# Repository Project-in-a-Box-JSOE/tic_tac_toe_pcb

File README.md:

# Tic-Tac-Toe

**A project series hosted by Project in a Box at UCSD**
> Workshop documentation [Tic-Tac-Toe Guide](https://docs.google.com/presentation/d/1Ihq2s2tMd88KeOKXIFUcY-OSz5jwRyJ442QZBEG7MqE/edit#slide=id.g12576c3175b_0_320)<br />
> More about [Project in a Box](https://pibucsd.org/)

## Overview
This workshop is oriented to assembling a handheld Tic-Tac-Toe board with surface mount devices (SMD) and reflow soldering.

The PCB was designed in Autodesk EAGLE

## BOM

| Component                    | Vendor                                                                                                     | Quantity   |
| ---------------------------- | ---------------------------------------------------------------------------------------------------------- | ---------- |
| NeoPixel Reverse Mount LEDs  | [Digikey](https://www.digikey.com/en/products/detail/adafruit-industries-llc/4960/14302512)                | 9          |
| ATMEGA328P-AUR              | [Digikey](https://www.digikey.com/en/products/detail/microchip-technology/ATMEGA328P-AUR/2357086)         | 1          |
| Tactile SMD Switch           | [Digikey](https://www.digikey.com/en/products/detail/te-connectivity-alcoswitch-switches/FSMSMTR/529671)   | 10         | 
| 5V-Regulator NCP1117ST50T3G  | [Digikey](https://www.digikey.com/en/products/detail/onsemi/NCP1117ST50T3G/1967217?utm_adgroup=Integrated%20Circuits%20%28ics%29&utm_source=google&utm_medium=cpc&utm_campaign=Shopping_Supplier_onsemi&utm_term=&utm_content=Integrated%20Circuits%20%28ics%29&gclid=Cj0KCQiAlMCOBhCZARIsANLid6Y771XCwKb85bAQFjVsh4KLFg09zcmp8NNUzVosYromvapvGWj7TFYaAqMzEALw_wcB)                                         | 1          | 
| Male Header (2x3-pins)       | [Digikey](https://www.digikey.com/en/products/detail/sullins-connector-solutions/PREC003DAAN-RC/2774891)   | 1          |
| DC Power Jack Socket         | [Digikey](https://www.digikey.com/en/products/detail/cui-devices/PJ-102AH/408448)                          | 1          |
| 330Ω SMD Resistor            | [Digikey](https://www.digikey.com/en/products/detail/yageo/RC1206FR-07330RL/731769?utm_adgroup=Yageo&utm_source=google&utm_medium=cpc&utm_campaign=Smart%20Shopping_Supplier_Yageo&utm_term=&utm_content=Yageo&gclid=Cj0KCQiAlMCOBhCZARIsANLid6Z2svdxXZcCLMl1CfXB-2cxl0jIykvjQrsu_GYfRR0vX5eyD9WpRuYaAu_oEALw_wcB)                                         | 1          |
| 10kΩ SMD Resistor            | [Digikey](https://www.digikey.com/en/products/detail/bourns-inc/CR0805-FX-1002ELF/3592928)                 | 1          |
| 0.1uF Ceramic SMD Capacitor  | [Digikey](https://www.digikey.com/en/products/detail/kyocera-avx/08055F104K4T2A/1024871?s=N4IgTCBcDaICwHYAcBaAzANgIxxVlAcgCIgC6AvkA)                                                                                                | 3          |
| 4.7uF Ceramic SMD Capacitor  | [Digikey](https://www.digikey.com/en/products/detail/samsung-electro-mechanics/CL21A475KAQNNNE/3886902)    | 1          |
| 10uF Tantalum SMD Capacitor  | [Digikey](https://www.digikey.com/en/products/detail/kyocera-avx/TAJR106M006RNJ/808827?utm_adgroup=Capacitors&utm_source=google&utm_medium=cpc&utm_campaign=Shopping_Supplier_AVX%20Corporation_8081_Co-op&utm_term=&utm_content=Capacitors&gclid=Cj0KCQiAlMCOBhCZARIsANLid6bJbctGY0qeTmGLRI9MiFk71J5VgDx9M5K57QbWr1aYRBVTJ_qByIAaAsGTEALw_wcB)                                         | 2          |
| 22pF Ceramic SMD Capacitor  | [Digikey](https://www.digikey.com/en/products/detail/kemet/C0805C220J5GACTU/411388)    | 2          |
| 16MHz SMD Cystal  | [Digikey](https://www.digikey.com/en/products/detail/ecs-inc/ECS-160-12-33-AGN-TR/9648827)    | 1          |
| TicTacToe PCB  | [JLCPCB](https://jlcpcb.com/)    | 1          |

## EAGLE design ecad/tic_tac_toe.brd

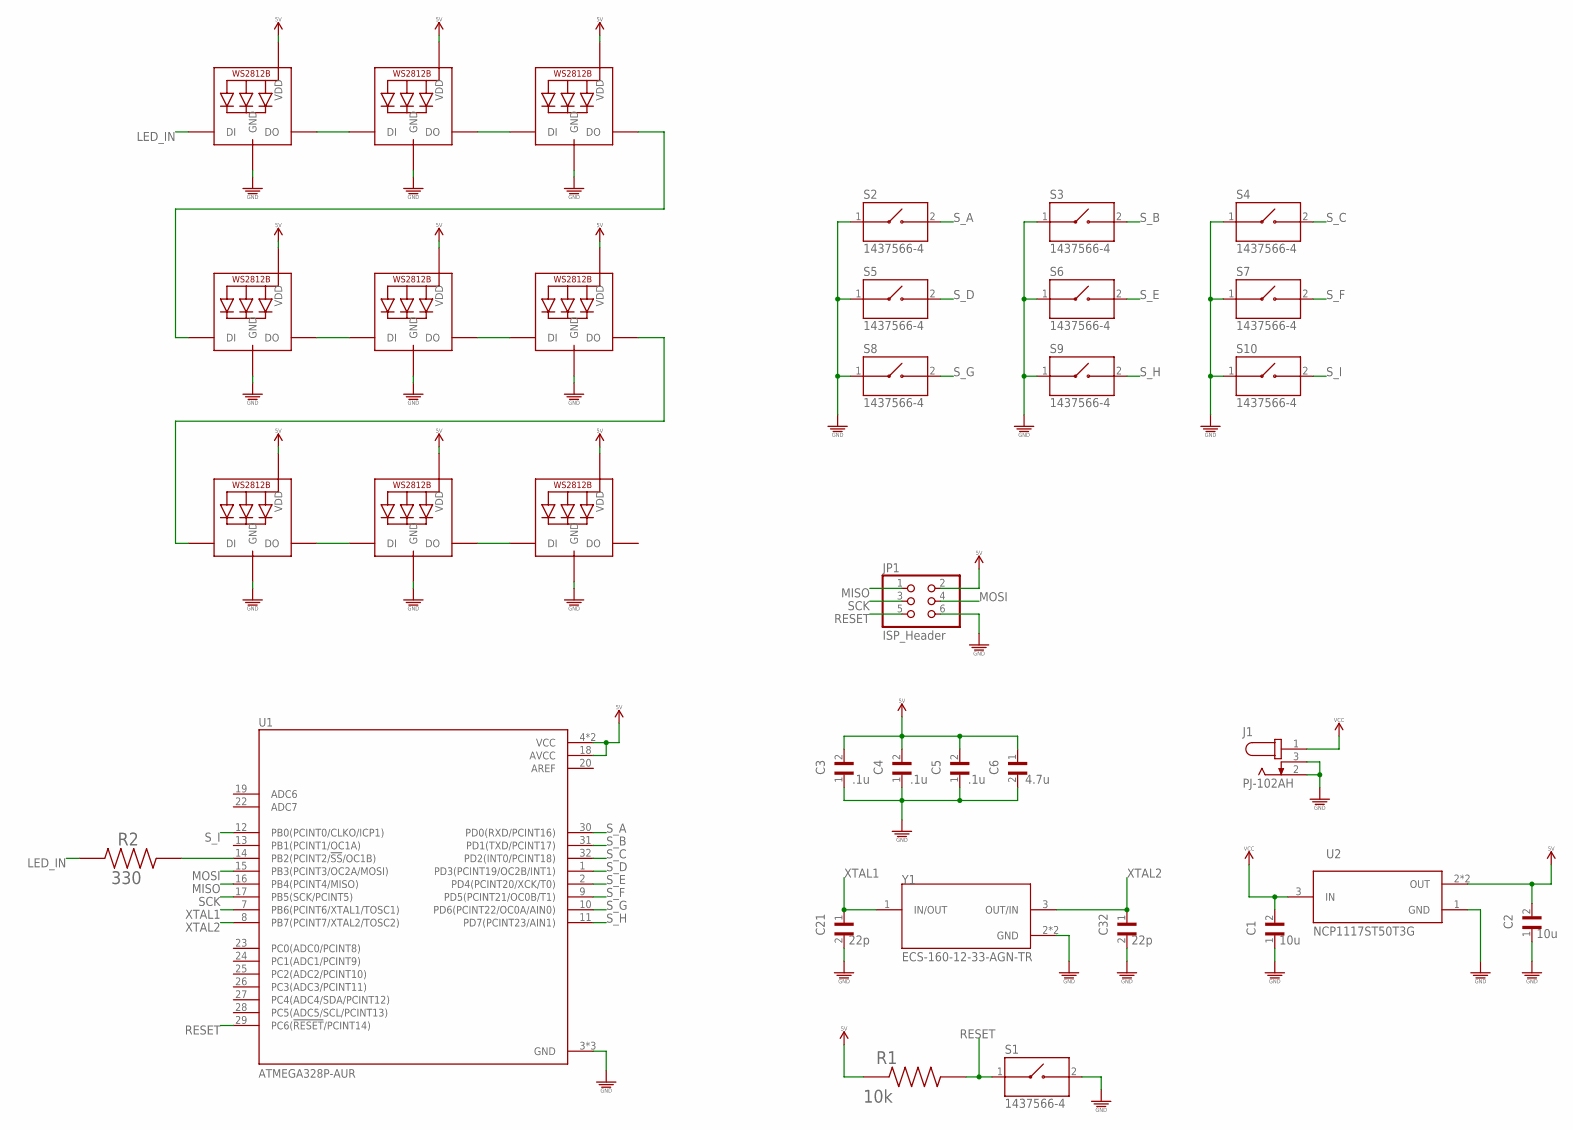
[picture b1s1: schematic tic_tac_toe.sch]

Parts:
C1, C2: 10u; CAPC2012X140N
C3, C4, C5: .1u; CAPC2012X140N
C6: 4.7u; CAPC2012X140N
C21, C32: 22p; CAPC2012X140N
J1: PJ-102AH; CUI_PJ-102AH
JP1: ISP_Header; 2X03
LED1, LED2, LED3, LED4, LED5, LED6, LED7, LED8, LED9: MICROBUILDER_WS2812B_SK6812E; MICROBUILDER_NEO3535_REVERSE
R1: 10k; RESC2012X60N
R2: 330; RESC3116X65N
S1, S2, S3, S4, S5, S6, S7, S8, S9, S10: 1437566-4; SW_1437566-4
U1: ATMEGA328P-AUR; QFP80P900X900X120-32N
U2: NCP1117ST50T3G; SOT230P700X180-4N
Y1: ECS-160-12-33-AGN-TR; XTAL_ECS-160-12-33-AGN-TR

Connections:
5V: C2.2, C3.2, C4.2, C5.2, C6.1, JP1.2, LED1.1-VDD (VDD), LED2.1-VDD (VDD), LED3.1-VDD (VDD), LED4.1-VDD (VDD), LED5.1-VDD (VDD), LED6.1-VDD (VDD), LED7.1-VDD (VDD), LED8.1-VDD (VDD), LED9.1-VDD (VDD), R1.1, U1.4 (VCC), U1.6 (VCC), U1.18 (AVCC), U2.2 (OUT), U2.4 (OUT)
AREF: U1.20 (AREF)
GND: C1.1, C2.1, C3.1, C4.1, C5.1, C6.2, C21.2, C32.2, J1.2, J1.3, JP1.6, LED1.3-GND (GND), LED2.3-GND (GND), LED3.3-GND (GND), LED4.3-GND (GND), LED5.3-GND (GND), LED6.3-GND (GND), LED7.3-GND (GND), LED8.3-GND (GND), LED9.3-GND (GND), S1.2, S2.1, S3.1, S4.1, S5.1, S6.1, S7.1, S8.1, S9.1, S10.1, U1.3 (GND), U1.5 (GND), U1.21 (GND), U2.1 (GND), Y1.2 (GND), Y1.4 (GND)
LED_IN: LED1.4-DIN (DI), R2.1
MISO: JP1.1, U1.16 (PB4(PCINT4/MISO))
MOSI: JP1.4, U1.15 (PB3(PCINT3/OC2A/MOSI))
unnamed: R2.2, U1.14 (PB2(PCINT2/!SS!/OC1B))
unnamed: LED1.2-DOUT (DO), LED2.4-DIN (DI)
unnamed: LED2.2-DOUT (DO), LED3.4-DIN (DI)
unnamed: LED4.2-DOUT (DO), LED5.4-DIN (DI)
unnamed: LED5.2-DOUT (DO), LED6.4-DIN (DI)
unnamed: LED7.2-DOUT (DO), LED8.4-DIN (DI)
unnamed: LED8.2-DOUT (DO), LED9.4-DIN (DI)
unnamed: LED3.2-DOUT (DO), LED4.4-DIN (DI)
unnamed: LED6.2-DOUT (DO), LED7.4-DIN (DI)
RESET: JP1.5, R1.2, S1.1, U1.29 (PC6(!RESET!/PCINT14))
SCK: JP1.3, U1.17 (PB5(SCK/PCINT5))
S_A: S2.2, U1.30 (PD0(RXD/PCINT16))
S_B: S3.2, U1.31 (PD1(TXD/PCINT17))
S_C: S4.2, U1.32 (PD2(INT0/PCINT18))
S_D: S5.2, U1.1 (PD3(PCINT19/OC2B/INT1))
S_E: S6.2, U1.2 (PD4(PCINT20/XCK/T0))
S_F: S7.2, U1.9 (PD5(PCINT21/OC0B/T1))
S_G: S8.2, U1.10 (PD6(PCINT22/OC0A/AIN0))
S_H: S9.2, U1.11 (PD7(PCINT23/AIN1))
S_I: S10.2, U1.12 (PB0(PCINT0/CLKO/ICP1))
VCC: C1.2, J1.1, U2.3 (IN)
XTAL1: C21.1, U1.7 (PB6(PCINT6/XTAL1/TOSC1)), Y1.1 (IN/OUT)
XTAL2: C32.1, U1.8 (PB7(PCINT7/XTAL2/TOSC2)), Y1.3 (OUT/IN)

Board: 2 copper layers, 34 parts (0 on the bottom side), 28 nets, no tracks yet.

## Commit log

2022-03-24 ecad
2022-03-24 remove ds store
2022-03-25 ecad, gerbers
2022-03-25 readme init
2022-03-26 code
2022-04-12 v3 sch
2022-04-12 remove cached ecad
2022-04-12 design rules dru
2022-04-12 readme BOM
2022-04-12 remove altium
2022-04-12 readme more
2022-05-05 documentation
